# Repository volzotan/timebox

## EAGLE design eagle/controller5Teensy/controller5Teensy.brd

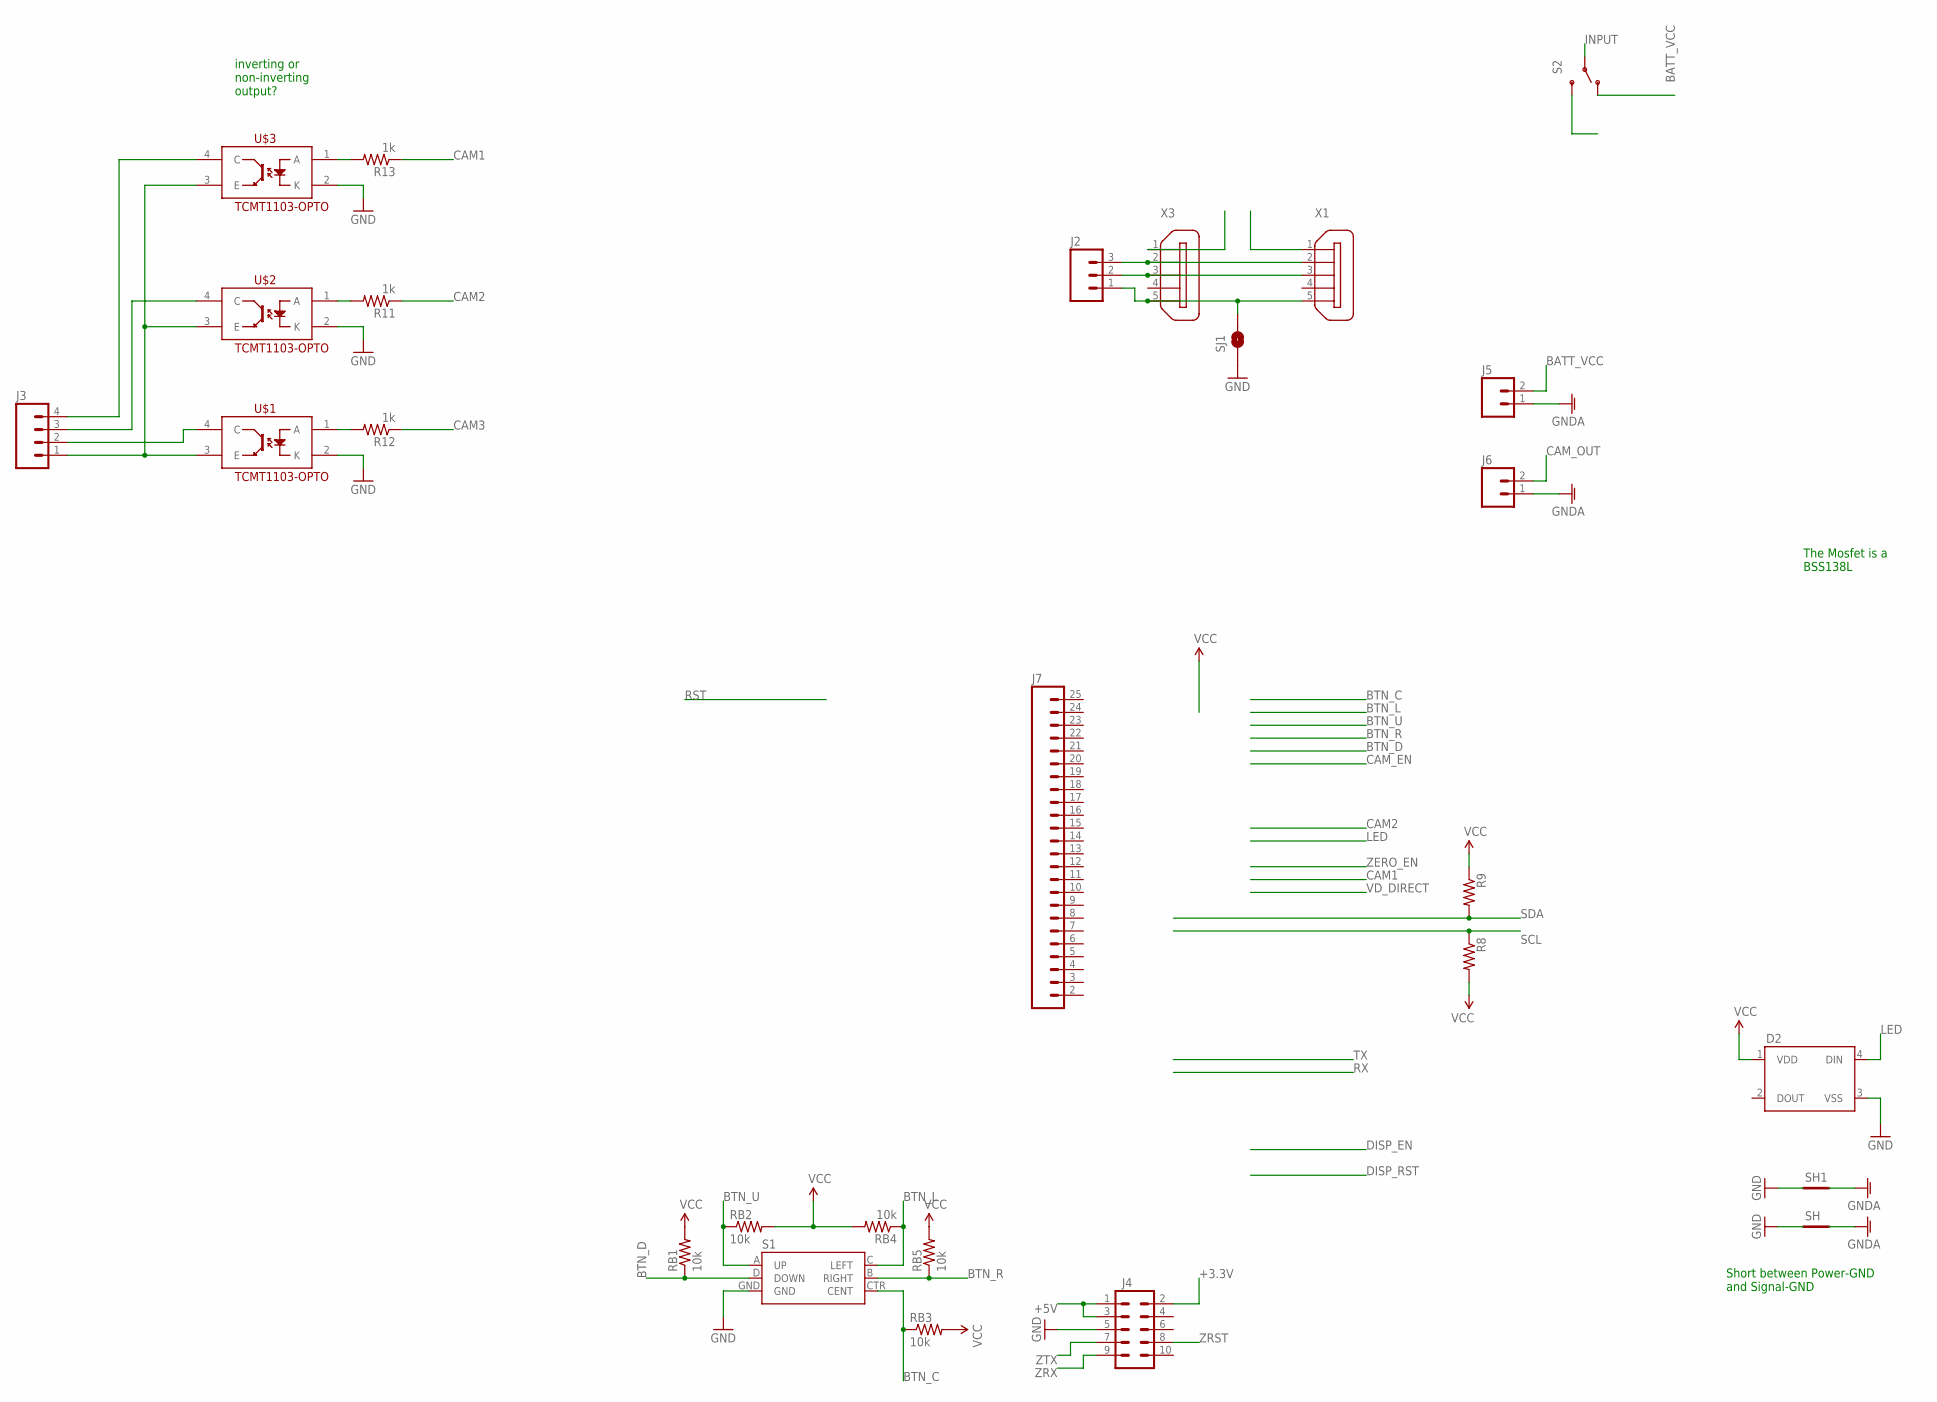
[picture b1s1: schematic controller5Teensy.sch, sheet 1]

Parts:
D2: WS2812B
J2: M03LOCK; 1X03_LOCK
J3: M04LOCK; 1X04_LOCK
J4: M05X2NO_SILK; 2X5_NOSILK
J5, J6: M023.5MM_LOCK; SCREWTERMINAL-3.5MM-2_LOCK
J7: M24; 1X24
R8, R9: RESISTOR1206; 1206
R11, R12, R13: 1k; 1206
RB1, RB2, RB3, RB4, RB5: 10k; 1206
S1: JOYSTICK_MINI
S2: SWITCH-SPDTPTH_LOCK; SWITCH-SPDT_LOCK.007S
SH, SH1: SHORT-HT5; SHORT_TOP-50
SJ1: SOLDERJUMPERNO; SJ_2S-NO
U$1, U$2, U$3: TCMT1103-OPTO; SSOP-4
X1, X3: ZX62D-B-5PA8

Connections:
+3.3V: J4.2
+5V: J4.1, J4.3
BATT_VCC: J5.2, S2.1 (O); also elsewhere on the board
BTN_C: RB3.1, S1.CTR (CENT)
BTN_D: RB1.1, S1.D (DOWN)
BTN_L: RB4.1, S1.C (LEFT)
BTN_R: RB5.1, S1.B (RIGHT)
BTN_U: RB2.1, S1.A (UP)
CAM1: R13.1
CAM2: R11.1
CAM3: R12.1
CAM_OUT: J6.2; also elsewhere on the board
GND: D2.3 (VSS), J4.5, S1.GND, SH.1, SH1.1, SJ1.1, U$1.2 (K), U$2.2 (K), U$3.2 (K); also elsewhere on the board
GNDA: J5.1, J6.1, SH.2, SH1.2
INPUT: S2.2; also elsewhere on the board
LED: D2.4 (DIN)
unnamed: J2.3, X1.2, X3.2
unnamed: J2.2, X1.3, X3.3
unnamed: J2.1, SJ1.2, X1.5, X3.5
unnamed: R11.2, U$2.1 (A)
unnamed: R12.2, U$1.1 (A)
unnamed: J3.1, U$1.3 (E), U$2.3 (E), U$3.3 (E)
unnamed: R13.2, U$3.1 (A)
unnamed: J3.2, U$1.4 (C)
unnamed: J3.3, U$2.4 (C)
unnamed: J3.4, U$3.4 (C)
SCL: R8.1; also elsewhere on the board
SDA: R9.2; also elsewhere on the board
VCC: D2.1 (VDD), R8.2, R9.1, RB1.2, RB2.2, RB3.2, RB4.2, RB5.2; also elsewhere on the board
ZRST: J4.8
ZRX: J4.9
ZTX: J4.7

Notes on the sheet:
Short between Power-GND and Signal-GND
The Mosfet is a BSS138L
inverting or non-inverting output?

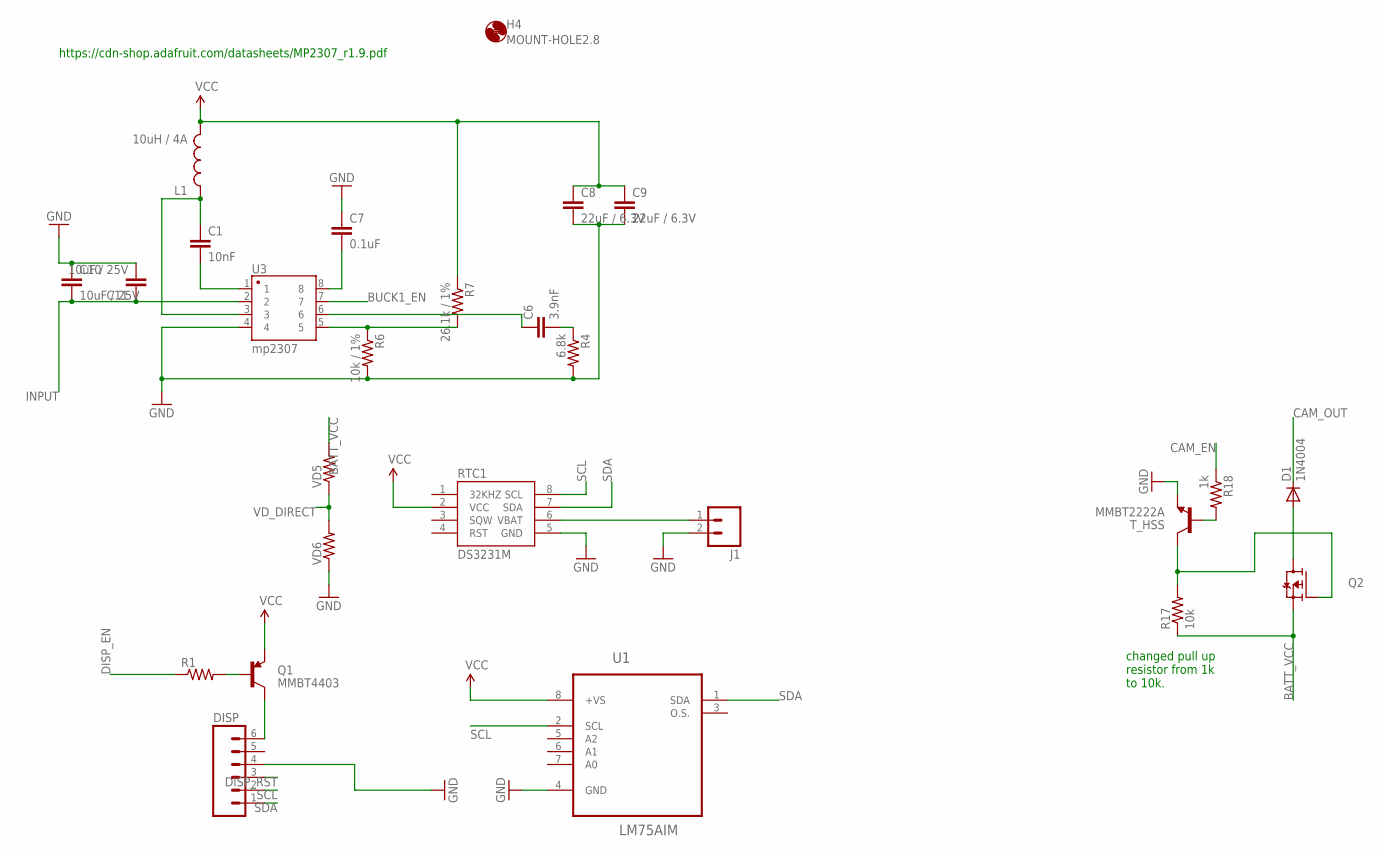
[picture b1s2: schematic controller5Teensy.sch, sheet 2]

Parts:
C1: 10nF; 1206
C6: 3.9nF; 1206
C7: 0.1uF; 1206
C8, C9: 22uF / 6.3V; 1206
C10, C11: 10uF / 25V; 1206
D1: 1N4004; DO41-10
DISP: M06FEMALE_LOCK; 1X06_FEMALE_LOCK.010
H4: MOUNT-HOLE2.8; 2,8
J1: M02LOCK_LONGPADS; 1X02_LOCK_LONGPADS
L1: 10uH / 4A; SDR0403
Q1: MMBT4403; SOT23-3
Q2: FDD4141TO252; TO252
R1: RESISTOR1206; 1206
R4: 6.8k; 1206
R6: 10k / 1%; 1206
R7: 26.1k / 1%; 1206
R17: 10k; 1206
R18: 1k; 1206
RTC1: DS3231M; SOIC8
T_HSS: MMBT2222A; SOT23-3
U1: LM75AIM; SOIC127P620X175-8N
U3: mp2307; SO08-UNIVERSAL
VD5, VD6: RESISTOR1206; 1206

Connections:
BATT_VCC: Q2.2 (S), R17.1, VD5.2; also elsewhere on the board
BUCK1_EN: U3.7
CAM_EN: R18.1
CAM_OUT: D1.C; also elsewhere on the board
DISP_EN: R1.1
DISP_RST: DISP.3
GND: C7.1, C8.2, C9.2, C10.1, C11.2, DISP.4, J1.2, R4.2, R6.2, RTC1.5 (GND), T_HSS.2 (E), U1.4 (GND), U3.4, VD6.1; also elsewhere on the board
INPUT: C10.2, C11.1, U3.2; also elsewhere on the board
unnamed: C1.1, L1.P$1 (1), U3.3
unnamed: DISP.6, Q1.3 (C)
unnamed: Q1.1 (B), R1.2
unnamed: C1.2, U3.1
unnamed: D1.A, Q2.3 (D)
unnamed: C7.2, U3.8
unnamed: R6.1, R7.2, U3.5
unnamed: C6.1, U3.6
unnamed: C6.2, R4.1
unnamed: R18.2, T_HSS.1 (B)
unnamed: Q2.1 (G), R17.2, T_HSS.3 (C)
SCL: DISP.2, RTC1.8 (SCL), U1.2 (SCL); also elsewhere on the board
SDA: DISP.1, RTC1.7 (SDA), U1.1 (SDA); also elsewhere on the board
VBAT: J1.1, RTC1.6 (VBAT)
VCC: C8.1, C9.1, L1.P$2 (2), Q1.2 (E), R7.1, RTC1.2 (VCC), U1.8 (+VS); also elsewhere on the board
VD_DIRECT: VD5.1, VD6.2

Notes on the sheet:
changed pull up resistor from 1k to 10k.
https://cdn-shop.adafruit.com/datasheets/MP2307_r1.9.pdf

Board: 2 copper layers, 54 parts (0 on the bottom side), 37 nets, no tracks yet.

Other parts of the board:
H3: MOUNT-HOLE2.8; 2,8

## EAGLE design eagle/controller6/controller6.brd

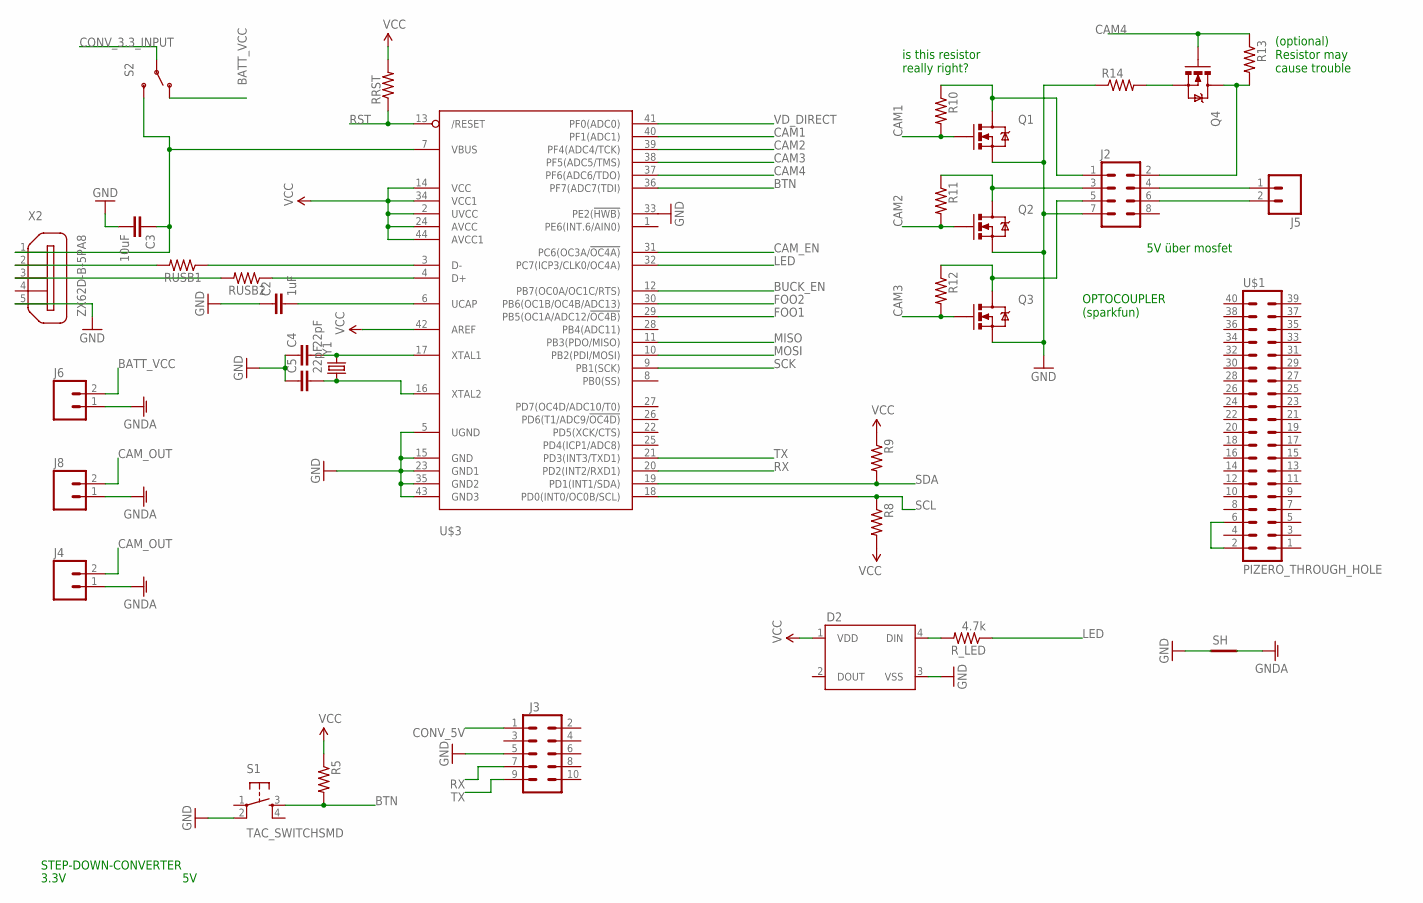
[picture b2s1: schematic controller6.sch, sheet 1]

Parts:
C2: 1uF; 1206
C3: 10uF; 0805
C4, C5: 22pF; 0805
D2: WS2812B
J2: M04X2; 2X4
J3: M05X2NO_SILK; 2X5_NOSILK
J4, J6, J8: M02LOCK; 1X02_LOCK
J5: M02PTH; 1X02
Q1, Q2, Q3, Q4: MOSFET-NCHANNELBSS138; SOT23-3
R5, R8, R9, R10, R11, R12, R13, R14: RESISTOR0805-RES; 0805
RRST: RESISTOR0805-RES; 0805
RUSB1, RUSB2: RESISTOR0805-RES; 0805
R_LED: 4.7k; 0805
S1: TAC_SWITCHSMD; TACTILE-SWITCH-SMD
S2: SWITCH-SPDTPTH_LOCK; SWITCH-SPDT_LOCK.007S
SH: SHORT-HT5; SHORT_TOP-50
U$1: PIZERO_THROUGH_HOLE; PIZERO_THOUGH_HOLE
U$3: ATMEGA32U4-AU; TQFP44
X2: ZX62D-B-5PA8
Y1: CRYSTALCRYSTAL-SMD-5X3-16MHZ; CRYSTAL-SMD-5X3

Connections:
BATT_VCC: J6.2, S2.1 (O); also elsewhere on the board
BTN: R5.2, S1.3, U$3.36 (PF7(ADC7(TDI))
BUCK_EN: U$3.12 (PB7(OC0A/OC1C/RTS)); also elsewhere on the board
CAM1: Q1.1 (G), R10.2, U$3.40 (PF1(ADC1))
CAM2: Q2.1 (G), R11.2, U$3.39 (PF4(ADC4/TCK))
CAM3: Q3.1 (G), R12.2, U$3.38 (PF5(ADC5/TMS))
CAM4: Q4.1 (G), R13.1, U$3.37 (PF6(ADC6/TDO))
CAM_EN: U$3.31 (PC6(OC3A/!OC4A))
CAM_OUT: J4.2, J8.2
CONV_3.3_INPUT: S2.2; also elsewhere on the board
CONV_5V: J3.1; also elsewhere on the board
FOO1: U$3.29 (PB5(OC1A/ADC12/!OC4B))
FOO2: U$3.30 (PB6(OC1B/OC4B/ADC13))
GND: C2.1, C3.2, C4.1, C5.1, D2.3 (VSS), J2.7, J3.5, Q1.2 (S), Q2.2 (S), Q3.2 (S), R14.1, S1.2, SH.1, U$3.5 (UGND), U$3.15 (GND), U$3.23 (GND1), U$3.33 (PE2(!HWB)), U$3.35 (GND2), U$3.43 (GND3), X2.5; also elsewhere on the board
GNDA: J4.1, J6.1, J8.1, SH.2
LED: R_LED.1, U$3.32 (PC7(ICP3/CLK0/OC4A))
MISO: U$3.11 (PB3(PDO/MISO)); also elsewhere on the board
MOSI: U$3.10 (PB2(PDI/MOSI)); also elsewhere on the board
unnamed: J2.4, J5.1
unnamed: RUSB1.1, U$3.3 (D-)
unnamed: RUSB2.1, U$3.4 (D+)
unnamed: J2.6, J5.2
unnamed: D2.4 (DIN), R_LED.2
unnamed: C4.2, U$3.17 (XTAL1), Y1.3 (2)
unnamed: C5.2, U$3.16 (XTAL2), Y1.1
unnamed: RUSB1.2, X2.2
unnamed: RUSB2.2, X2.3
unnamed: J2.2, Q4.3 (D), R13.2
unnamed: Q4.2 (S), R14.2
unnamed: U$1.2, U$1.6
unnamed: C2.2, U$3.6 (UCAP)
unnamed: C3.1, S2.3 (S), U$3.7 (VBUS), X2.1
unnamed: J2.1, Q1.3 (D), R10.1
unnamed: J2.3, Q2.3 (D), R11.1
unnamed: J2.5, Q3.3 (D), R12.1
RST: RRST.1, U$3.13 (/RESET); also elsewhere on the board
RX: J3.7, U$3.20 (PD2(INT2/RXD1))
SCK: U$3.9 (PB1(SCK)); also elsewhere on the board
SCL: R8.1, U$3.18 (PD0(INT0/OC0B/SCL)); also elsewhere on the board
SDA: R9.2, U$3.19 (PD1(INT1/SDA)); also elsewhere on the board
TX: J3.9, U$3.21 (PD3(INT3/TXD1))
VCC: D2.1 (VDD), R5.1, R8.2, R9.1, RRST.2, U$3.2 (UVCC), U$3.14 (VCC), U$3.24 (AVCC), U$3.34 (VCC1), U$3.42 (AREF), U$3.44 (AVCC1); also elsewhere on the board
VD_DIRECT: U$3.41 (PF0(ADC0)); also elsewhere on the board

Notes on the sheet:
STEP-DOWN-CONVERTER
3.3V
5V über mosfet
(optional) Resistor may cause trouble
is this resistor really right?
OPTOCOUPLER (sparkfun)

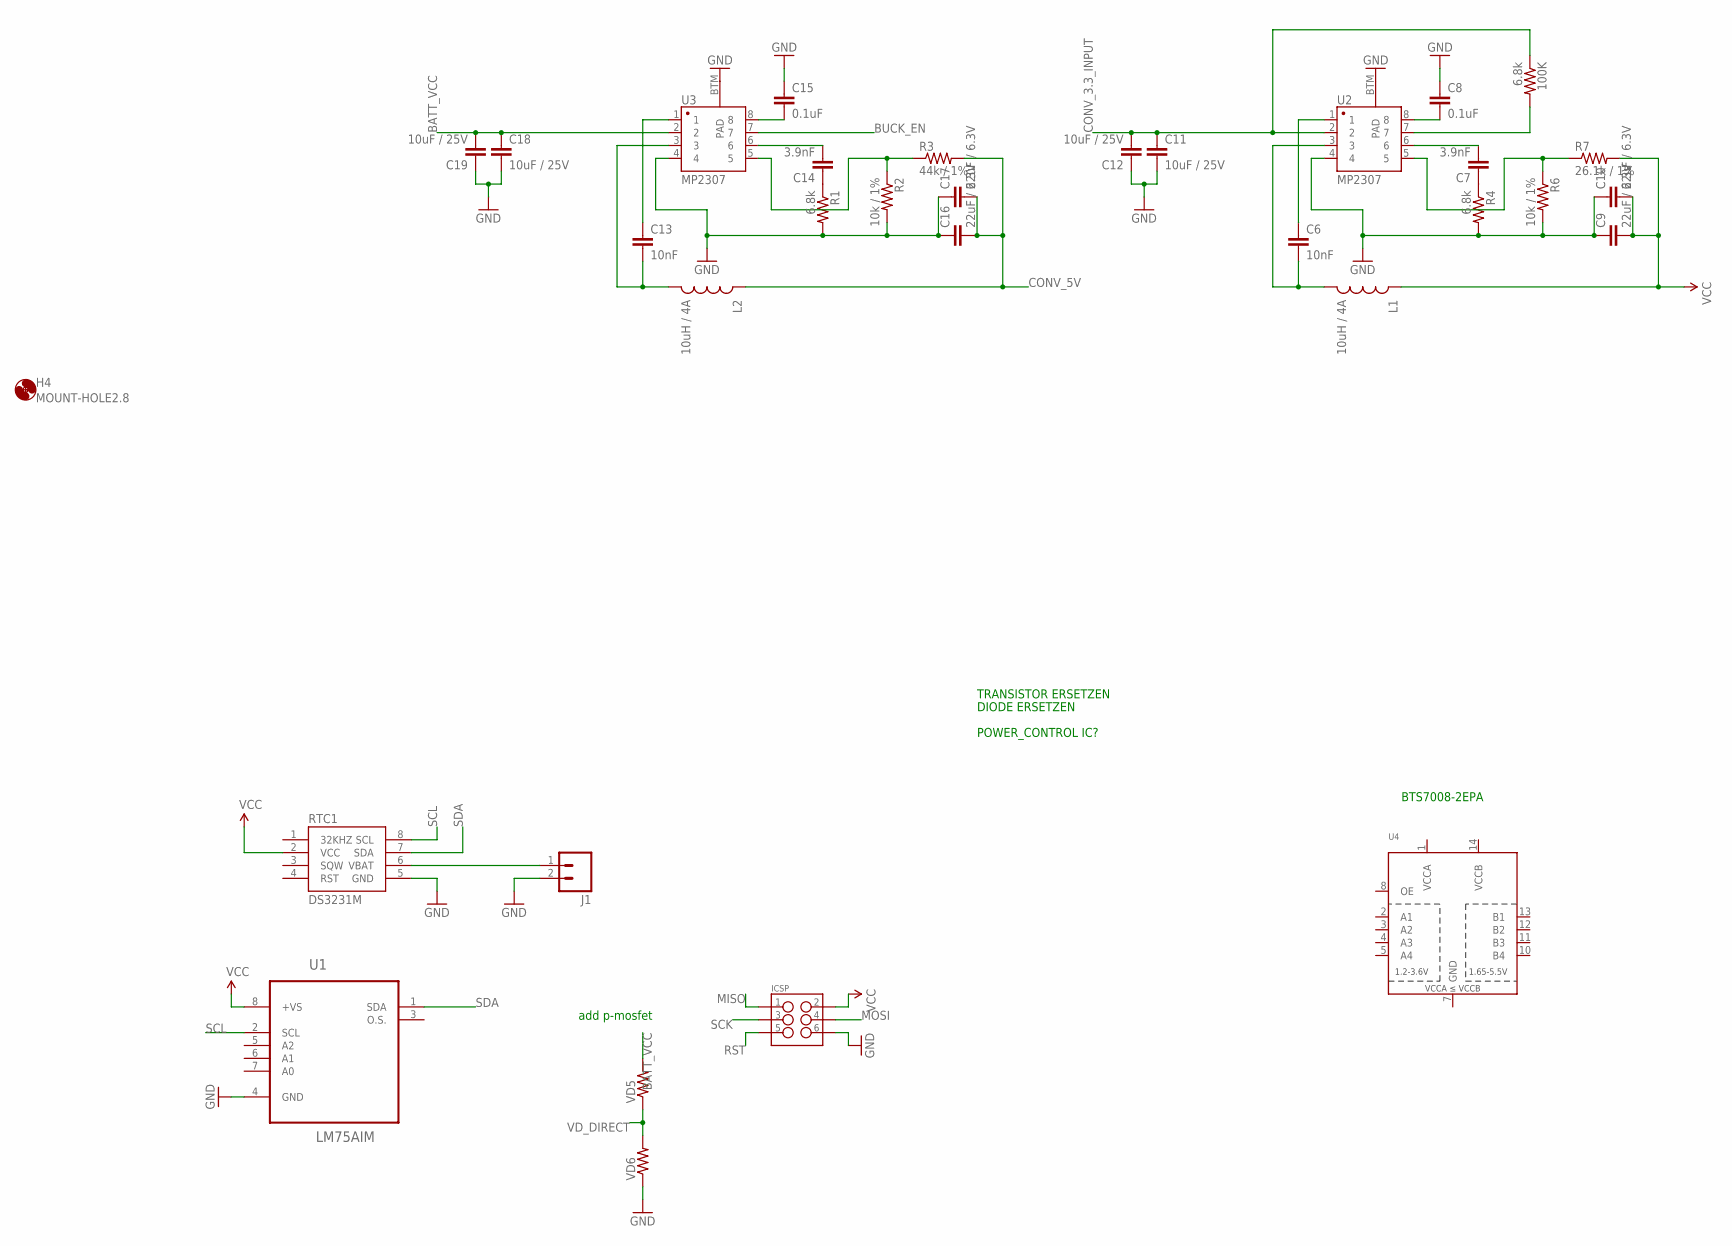
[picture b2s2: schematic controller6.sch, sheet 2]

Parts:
100K: 6.8k; 0805
C6, C13: 10nF; 1206
C7, C14: 3.9nF; 0805
C8, C15: 0.1uF; 0805
C9, C10, C16, C17: 22uF / 6.3V; 1206
C11, C12, C18, C19: 10uF / 25V; 1206
H4: MOUNT-HOLE2.8; 2,8
ICSP: M03X2FEMALE; 2X3
J1: M02LOCK_LONGPADS; 1X02_LOCK_LONGPADS
L1, L2: 10uH / 4A; SDR0403
R1, R4: 6.8k; 0805
R2, R6: 10k / 1%; 0805
R3: 44k / 1%; 0805
R7: 26.1k / 1%; 0805
RTC1: DS3231M; SOIC8
U1: LM75AIM; SOIC127P620X175-8N
U2, U3: MP2307; SO08
U4: TXB0104PWRSOIC14; SO14
VD5, VD6: RESISTOR1206; 1206

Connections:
BATT_VCC: C18.1, C19.2, U3.2, VD5.2; also elsewhere on the board
BUCK_EN: U3.7; also elsewhere on the board
CONV_3.3_INPUT: 100K.1, C11.1, C12.2, U2.2; also elsewhere on the board
CONV_5V: C16.2, C17.2, L2.P$1 (1), R3.2; also elsewhere on the board
GND: C8.1, C9.1, C10.1, C11.2, C12.1, C15.1, C16.1, C17.1, C18.2, C19.1, ICSP.6, J1.2, R1.2, R2.2, R4.2, R6.2, RTC1.5 (GND), U1.4 (GND), U2.4, U2.BTM (PAD), U3.4, U3.BTM (PAD), VD6.1; also elsewhere on the board
MISO: ICSP.1; also elsewhere on the board
MOSI: ICSP.4; also elsewhere on the board
unnamed: 100K.2, U2.7
unnamed: C6.1, U2.1
unnamed: C8.2, U2.8
unnamed: C6.2, L1.P$2 (2), U2.3
unnamed: C7.1, R4.1
unnamed: C7.2, U2.6
unnamed: R6.1, R7.1, U2.5
unnamed: C15.2, U3.8
unnamed: C13.2, L2.P$2 (2), U3.3
unnamed: C13.1, U3.1
unnamed: C14.1, R1.1
unnamed: C14.2, U3.6
unnamed: R2.1, R3.1, U3.5
RST: ICSP.5; also elsewhere on the board
SCK: ICSP.3; also elsewhere on the board
SCL: RTC1.8 (SCL), U1.2 (SCL); also elsewhere on the board
SDA: RTC1.7 (SDA), U1.1 (SDA); also elsewhere on the board
VBAT: J1.1, RTC1.6 (VBAT)
VCC: C9.2, C10.2, ICSP.2, L1.P$1 (1), R7.2, RTC1.2 (VCC), U1.8 (+VS); also elsewhere on the board
VD_DIRECT: VD5.1, VD6.2; also elsewhere on the board

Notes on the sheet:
TRANSISTOR ERSETZEN
DIODE ERSETZEN
POWER_CONTROL IC?
add p-mosfet
BTS7008-2EPA

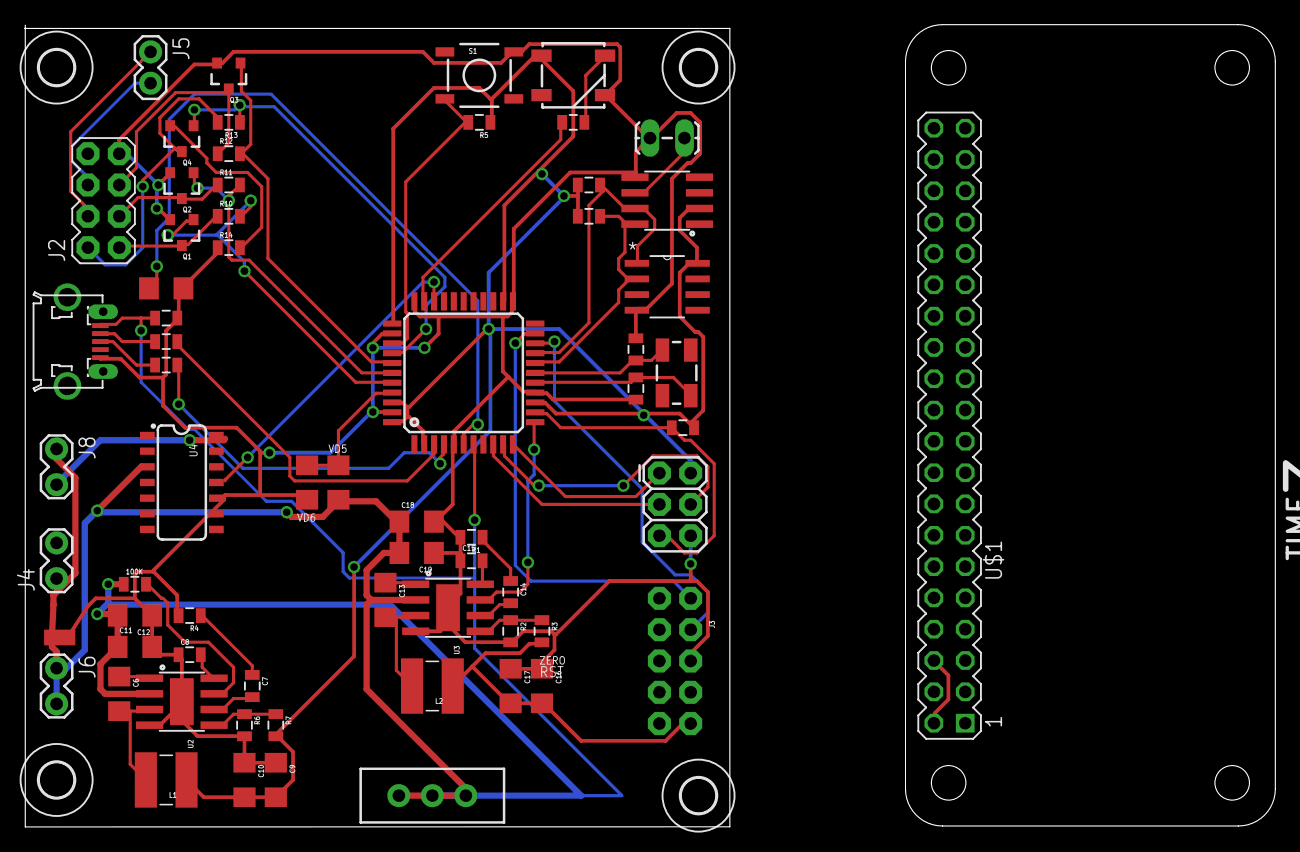
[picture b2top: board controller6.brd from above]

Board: 2 copper layers, 101.4 x 65.1 mm, 70 parts (0 on the bottom side), 54 nets.

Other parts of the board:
H1, H2, H3: MOUNT-HOLE2.8; 2,8

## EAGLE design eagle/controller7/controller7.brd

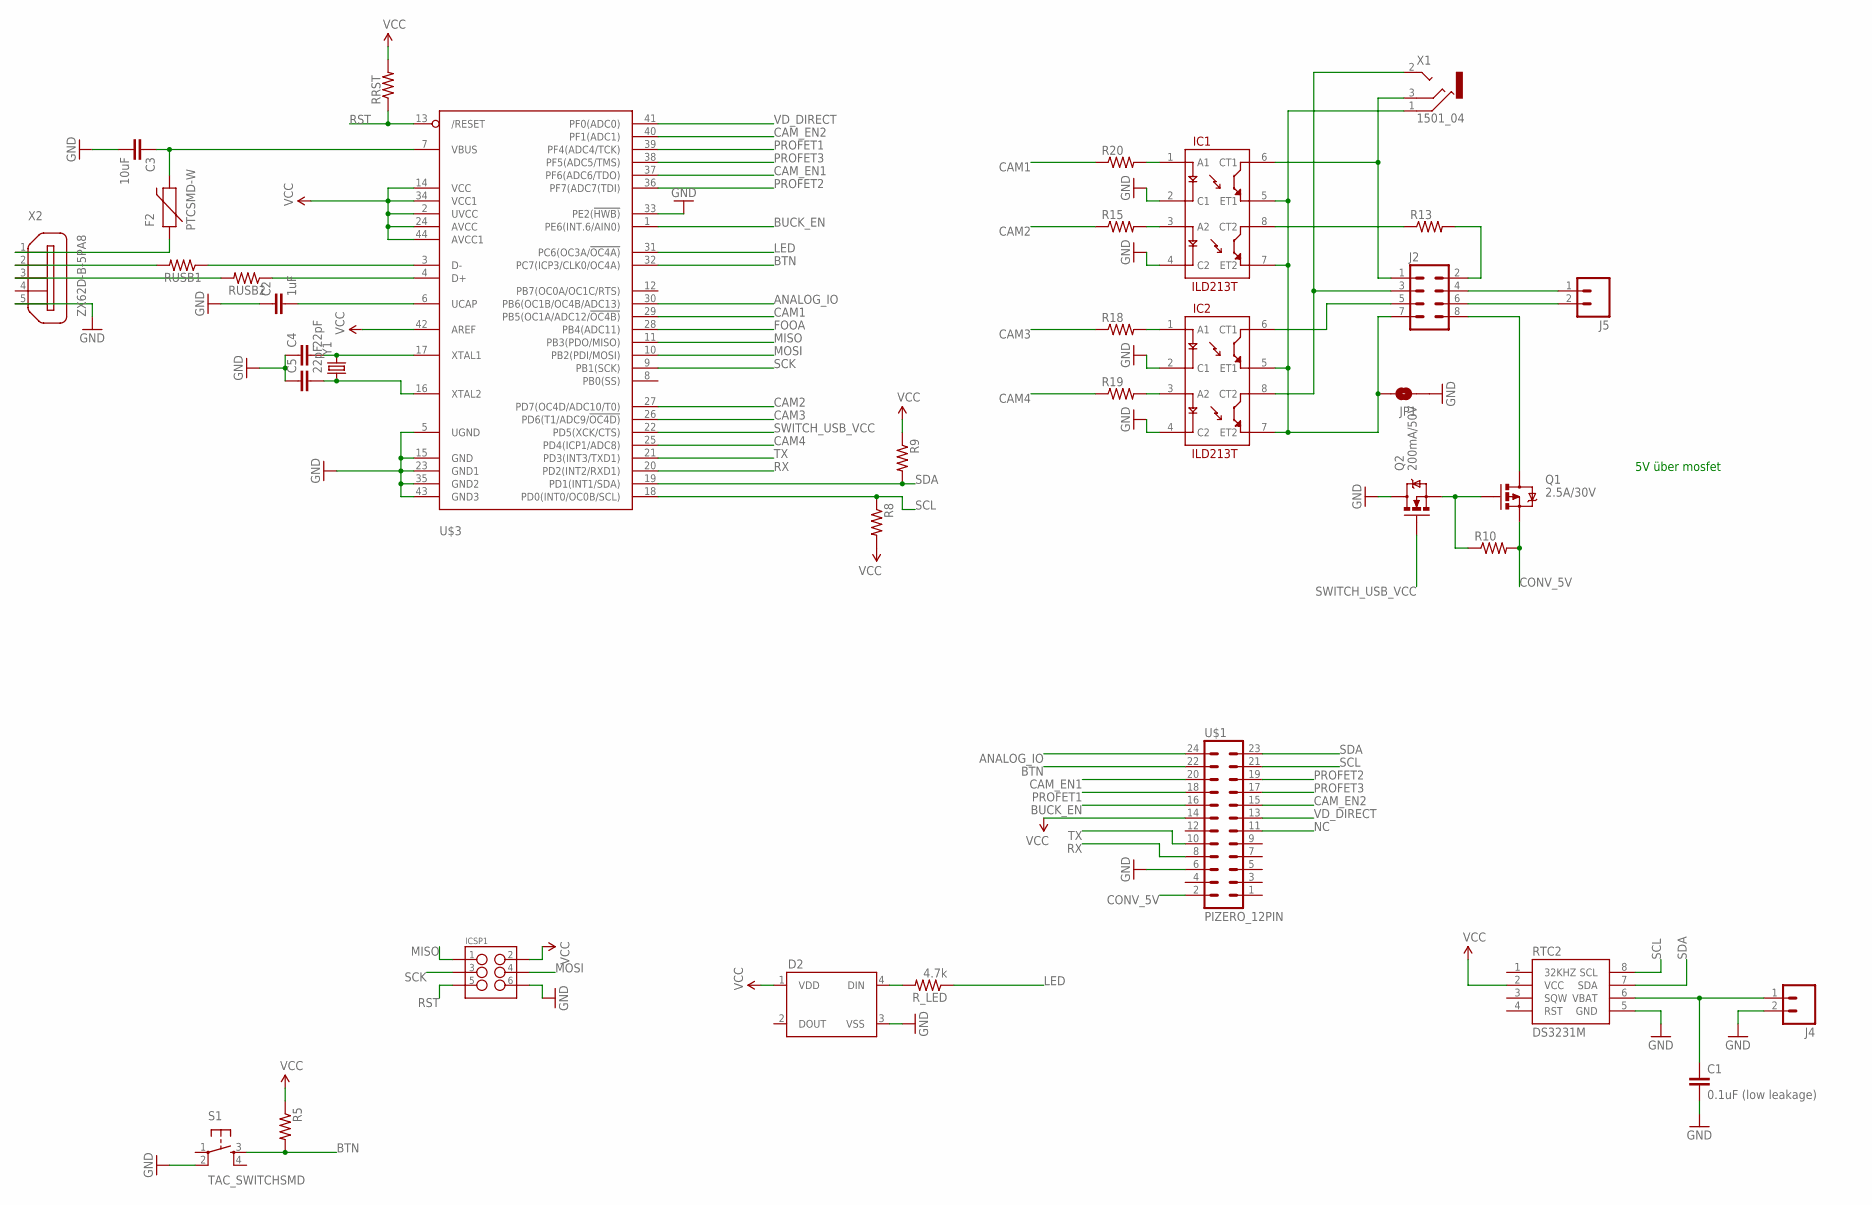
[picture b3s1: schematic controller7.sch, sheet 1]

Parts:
C1: 0.1uF (low leakage); 1206
C2: 1uF; 1206
C3: 10uF; 1206
C4, C5: 22pF; 0805
D2: WS2812B
F2: PTCSMD-W; PTC-1206-WIDE
IC1, IC2: ILD213T; SO08
ICSP1: M03X2FEMALE; 2X3
J2: M04X2; 2X4
J4, J5: M02PTH; 1X02
JP1: JUMPER-PAD-2-NOYES_SILK; PAD-JUMPER-2-NO_YES_SILK
Q1: 2.5A/30V; SOT23-3
Q2: 200mA/50V; SOT23-3
R5, R8, R9, R13: RESISTOR1206; 1206
R10, R15, R18, R19, R20: RESISTOR0805-RES; 0805
RRST: RESISTOR1206; 1206
RTC2: DS3231M; SOIC8
RUSB1, RUSB2: RESISTOR1206; 1206
R_LED: 4.7k; 1206
S1: TAC_SWITCHSMD; TACTILE-PTH
U$1: PIZERO_12PIN
U$3: ATMEGA32U4-AU; TQFP44
X1: 1501_04; 1501_05
X2: ZX62D-B-5PA8
Y1: CRYSTALCRYSTAL-SMD-5X3-16MHZ; CRYSTAL-SMD-5X3

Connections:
ANALOG_IO: U$1.24, U$3.30 (PB6(OC1B/OC4B/ADC13))
BTN: R5.2, S1.3, U$1.22, U$3.32 (PC7(ICP3/CLK0/OC4A))
BUCK_EN: U$1.16, U$3.1 (PE6(INT.6/AIN0))
CAM1: R20.1, U$3.29 (PB5(OC1A/ADC12/!OC4B))
CAM2: R15.1, U$3.27 (PD7(OC4D/ADC10/T0))
CAM3: R18.1, U$3.26 (PD6(T1/ADC9/!OC4D))
CAM4: R19.1, U$3.25 (PD4(ICP1/ADC8))
CAM_EN1: U$1.20, U$3.37 (PF6(ADC6/TDO))
CAM_EN2: U$1.15, U$3.40 (PF1(ADC1))
CONV_5V: Q1.2 (S), R10.2, U$1.2
FOOA: U$3.28 (PB4(ADC11))
GND: C1.2, C2.1, C3.2, C4.1, C5.1, D2.3 (VSS), IC1.2 (C1), IC1.4 (C2), IC2.2 (C1), IC2.4 (C2), ICSP1.6, J4.2, JP1.1, Q2.3 (D), RTC2.5 (GND), S1.2, U$1.6, U$3.5 (UGND), U$3.15 (GND), U$3.23 (GND1), U$3.33 (PE2(!HWB)), U$3.35 (GND2), U$3.43 (GND3), X2.5
LED: R_LED.1, U$3.31 (PC6(OC3A/!OC4A))
MISO: ICSP1.1, U$3.11 (PB3(PDO/MISO))
MOSI: ICSP1.4, U$3.10 (PB2(PDI/MOSI))
unnamed: J2.4, J5.1
unnamed: RUSB1.1, U$3.3 (D-)
unnamed: RUSB2.1, U$3.4 (D+)
unnamed: J2.6, J5.2
unnamed: D2.4 (DIN), R_LED.2
unnamed: C4.2, U$3.17 (XTAL1), Y1.3 (2)
unnamed: C5.2, U$3.16 (XTAL2), Y1.1
unnamed: RUSB1.2, X2.2
unnamed: RUSB2.2, X2.3
unnamed: IC2.1 (A1), R18.2
unnamed: IC2.3 (A2), R19.2
unnamed: IC1.3 (A2), R15.2
unnamed: J2.2, R13.2
unnamed: IC1.8 (CT2), R13.1
unnamed: IC1.1 (A1), R20.2
unnamed: C2.2, U$3.6 (UCAP)
unnamed: C3.1, F2.2, U$3.7 (VBUS)
unnamed: IC1.6 (CT1), J2.1, X1.3
unnamed: IC2.8 (CT2), J2.3, X1.2
unnamed: IC2.6 (CT1), J2.5
unnamed: IC1.5 (ET1), IC1.7 (ET2), IC2.5 (ET1), IC2.7 (ET2), J2.7, JP1.2, X1.1
unnamed: J2.8, Q1.3 (D)
unnamed: Q1.1 (G), Q2.2 (S), R10.1
unnamed: F2.1, X2.1
unnamed: C1.1, J4.1, RTC2.6 (VBAT)
NC: U$1.11
PROFET1: U$1.18, U$3.39 (PF4(ADC4/TCK))
PROFET2: U$1.19, U$3.36 (PF7(ADC7(TDI))
PROFET3: U$1.17, U$3.38 (PF5(ADC5/TMS))
RST: ICSP1.5, RRST.1, U$3.13 (/RESET)
RX: U$1.8, U$3.20 (PD2(INT2/RXD1))
SCK: ICSP1.3, U$3.9 (PB1(SCK))
SCL: R8.1, RTC2.8 (SCL), U$1.21, U$3.18 (PD0(INT0/OC0B/SCL))
SDA: R9.2, RTC2.7 (SDA), U$1.23, U$3.19 (PD1(INT1/SDA))
SWITCH_USB_VCC: Q2.1 (G), U$3.22 (PD5(XCK/CTS))
TX: U$1.10, U$3.21 (PD3(INT3/TXD1))
VCC: D2.1 (VDD), ICSP1.2, R5.1, R8.2, R9.1, RRST.2, RTC2.2 (VCC), U$1.14, U$3.2 (UVCC), U$3.14 (VCC), U$3.24 (AVCC), U$3.34 (VCC1), U$3.42 (AREF), U$3.44 (AVCC1)
VD_DIRECT: U$1.13, U$3.41 (PF0(ADC0))

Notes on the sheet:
5V über mosfet

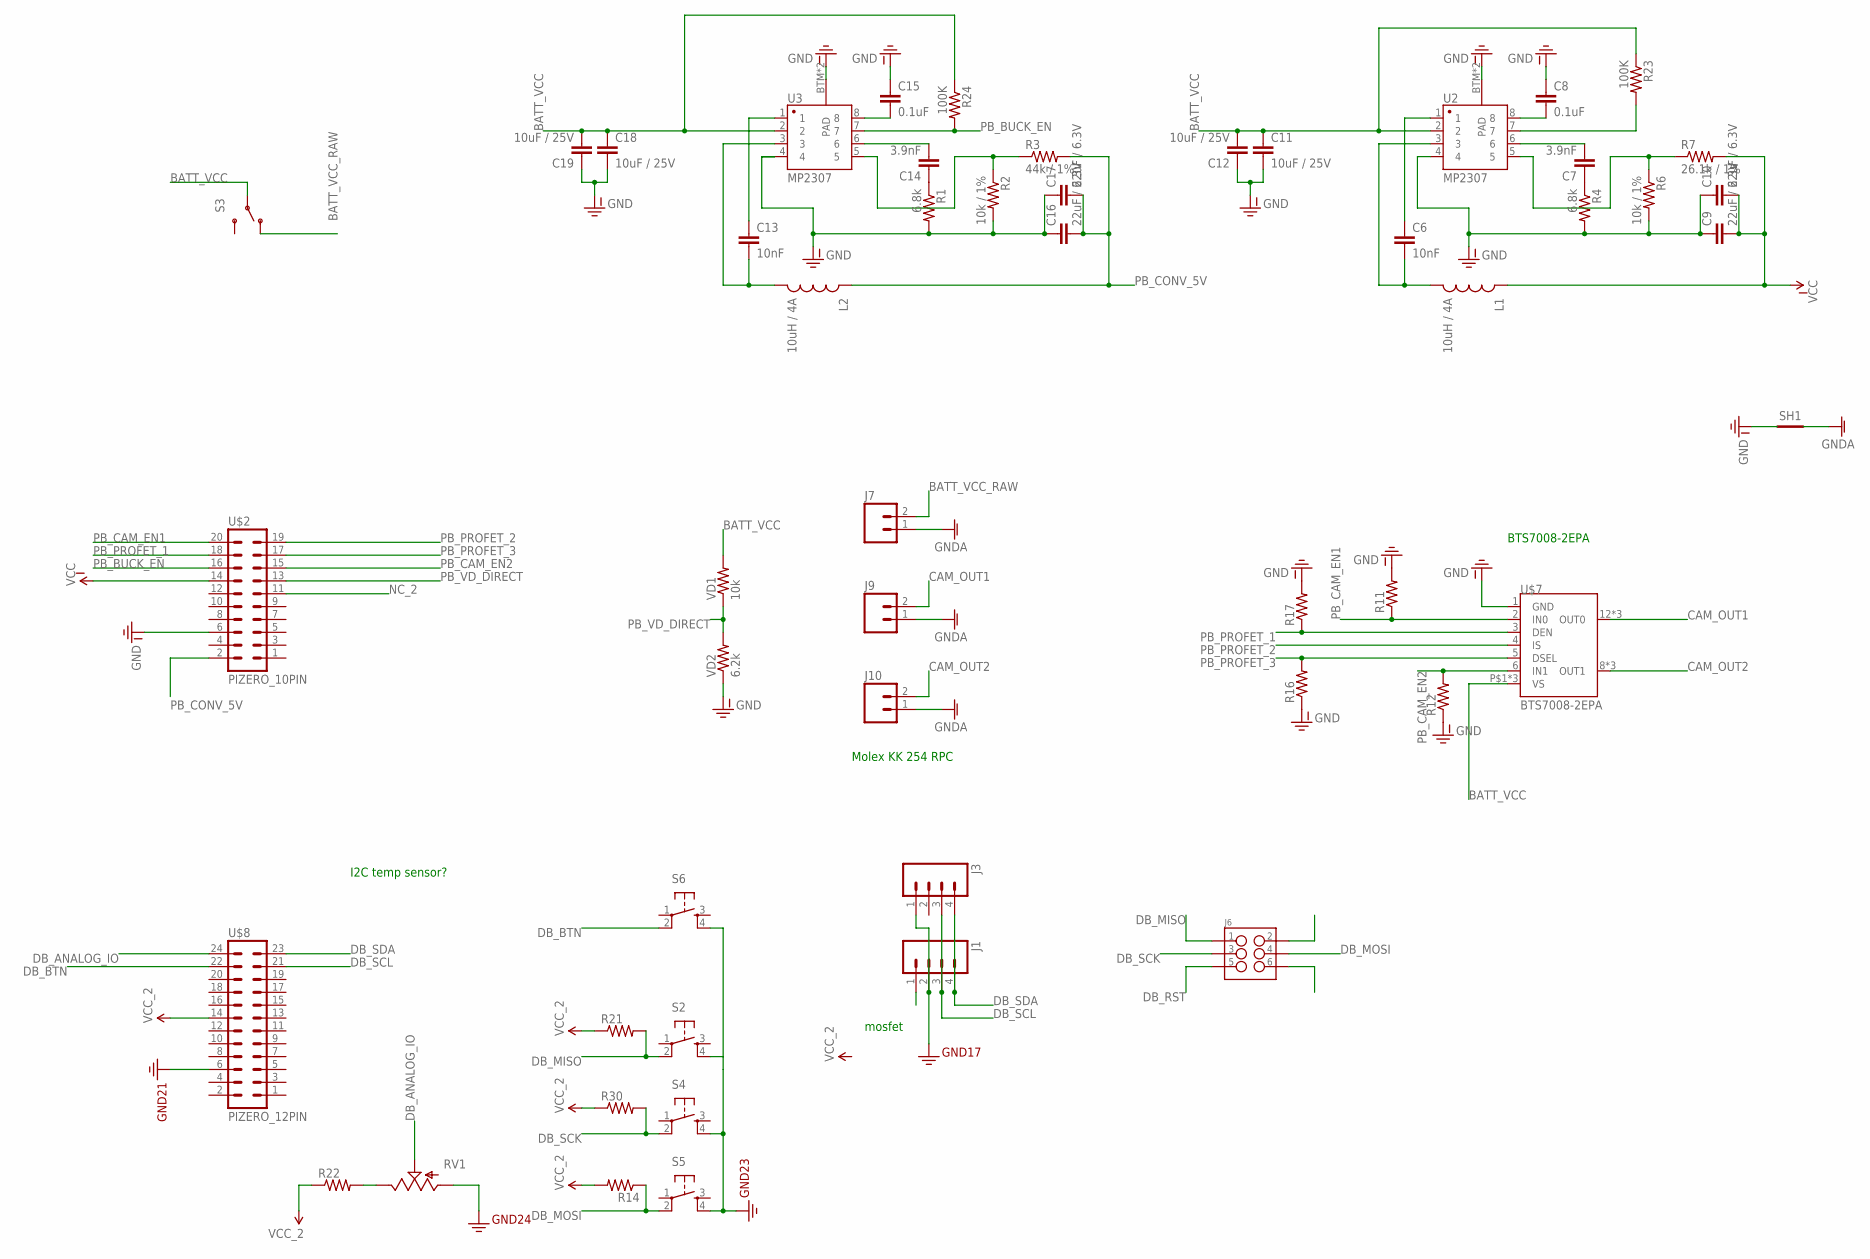
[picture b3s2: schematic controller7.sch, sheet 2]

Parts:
C6, C13: 10nF; 1206
C7, C14: 3.9nF; 0805
C8, C15: 0.1uF; 0805
C9, C10, C16, C17: 22uF / 6.3V; 1206
C11, C12, C18, C19: 10uF / 25V; 1206
J1, J3: M04LOCK; 1X04_LOCK
J6: M03X2FEMALE; 2X3
J7, J9, J10: M02LOCK; 1X02_LOCK
L1, L2: 10uH / 4A; SRU1038
R1, R4: 6.8k; 0805
R2, R6: 10k / 1%; 0805
R3: 44k / 1%; 0805
R7: 26.1k / 1%; 0805
R11, R12, R14, R16, R17, R21, R22, R30: RESISTOR1206; 1206
R23, R24: 100K; 0805
RV1: POT; ALPS_POT
S2, S4, S5, S6: TAC_SWITCHPTH; TACTILE-PTH
S3: SWITCH-SPDTPTH_LOCK; SWITCH-SPDT_LOCK.007S
SH1: SHORT-HT5; SHORT_TOP-50
U2, U3: MP2307; SO08
U$2: PIZERO_10PIN
U$7: BTS7008-2EPA; SOIC-14-PAD
U$8: PIZERO_12PIN
VD1: 10k; 1206
VD2: 6.2k; 1206

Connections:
3.3V: J1.2, J3.1, RV1.P$3 (A), S2.4, S4.4, S5.4, S6.4, U$8.6
BATT_VCC: C11.1, C12.2, C18.1, C19.2, R23.1, R24.1, S3.2, U2.2, U3.2, U$7.P$1 (VS), U$7.P$2 (VS), U$7.VS, VD1.2
BATT_VCC_RAW: J7.2, S3.1 (O)
CAM_OUT1: J9.2, U$7.12 (OUT0), U$7.13 (OUT0), U$7.14 (OUT0)
CAM_OUT2: J10.2, U$7.8 (OUT1), U$7.9 (OUT1), U$7.10 (OUT1)
DB_ANALOG_IO: RV1.P$2 (S), U$8.24
DB_BTN: S6.2, U$8.22
DB_MISO: J6.1, R21.2, S2.2
DB_MOSI: J6.4, R14.1, S5.2
DB_RST: J6.5
DB_SCK: J6.3, R30.2, S4.2
DB_SCL: J1.3, J3.3, U$8.21
DB_SDA: J1.4, J3.4, U$8.23
GND-ISO: C8.1, C9.1, C10.1, C11.2, C12.1, C15.1, C16.1, C17.1, C18.2, C19.1, R1.2, R2.2, R4.2, R6.2, R11.2, R12.1, R16.1, R17.2, SH1.1, U2.4, U2.BTM (PAD), U2.P$1 (PAD), U3.4, U3.BTM (PAD), U3.P$1 (PAD), U$2.6, U$7.1 (GND), VD2.1
GNDA: J7.1, J9.1, J10.1, SH1.2
unnamed: R23.2, U2.7
unnamed: C6.1, U2.1
unnamed: C8.2, U2.8
unnamed: C6.2, L1.2, U2.3
unnamed: C7.1, R4.1
unnamed: C7.2, U2.6
unnamed: R6.1, R7.1, U2.5
unnamed: C15.2, U3.8
unnamed: C13.2, L2.2, U3.3
unnamed: C13.1, U3.1
unnamed: C14.1, R1.1
unnamed: C14.2, U3.6
unnamed: R2.1, R3.1, U3.5
unnamed: R22.2, RV1.P$1 (E)
NC_2: U$2.11
PB_BUCK_EN: R24.2, U3.7, U$2.16
PB_CAM_EN1: R11.1, U$2.20, U$7.2 (IN0)
PB_CAM_EN2: R12.2, U$2.15, U$7.6 (IN1)
PB_CONV_5V: C16.2, C17.2, L2.1, R3.2, U$2.2
PB_PROFET_1: R17.1, U$2.18, U$7.3 (DEN)
PB_PROFET_2: U$2.19, U$7.4 (IS)
PB_PROFET_3: R16.2, U$2.17, U$7.5 (DSEL)
PB_VD_DIRECT: U$2.13, VD1.1, VD2.2
VCC-ISO: C9.2, C10.2, L1.1, R7.2, U$2.14
VCC_2: R14.2, R21.1, R22.1, R30.1, U$8.14

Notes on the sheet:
BTS7008-2EPA
mosfet
I2C temp sensor?
Molex KK 254 RPC

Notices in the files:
parts and their libraries:
SparkFun-Connectors: Licensing: Creative Commons ShareAlike 4.0 International - https://creativecommons.org/licenses/by-sa/4.0
